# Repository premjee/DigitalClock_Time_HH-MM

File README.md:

# DigitalClock_Time_HH-MM
Displays time in HH:MM format using 7seg led
8 bit microcontroller is used to set and read time from RTC and display time in 7 segment LED.
Schematic of the project is addeded

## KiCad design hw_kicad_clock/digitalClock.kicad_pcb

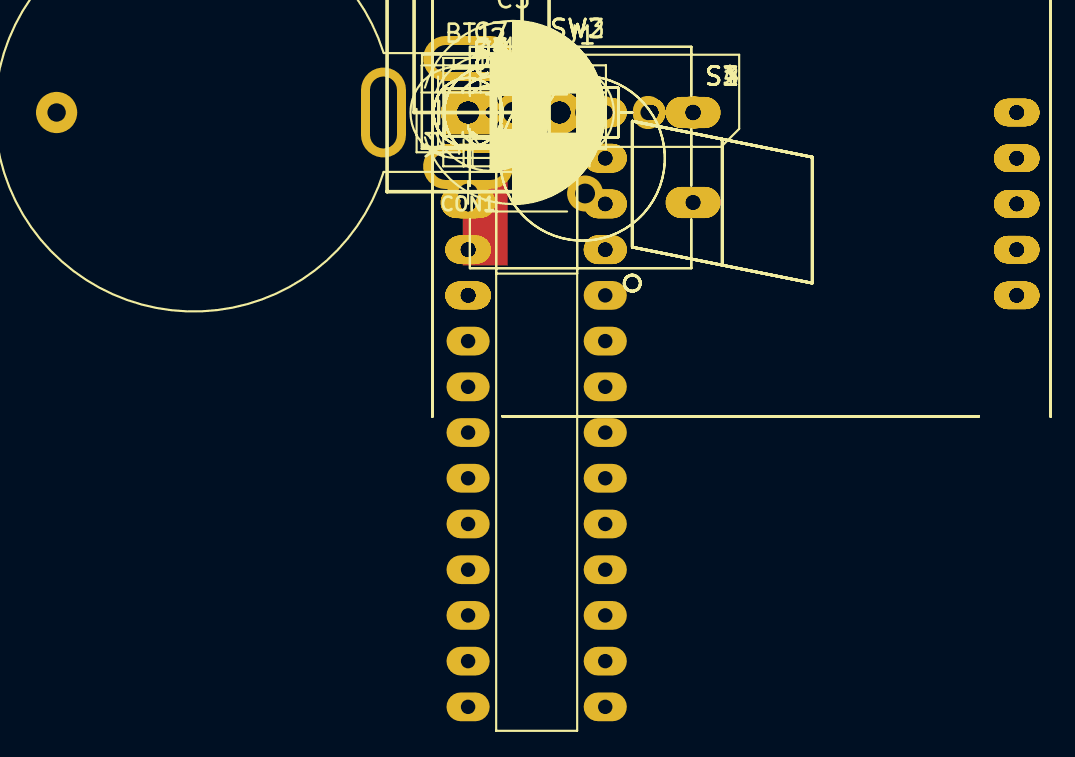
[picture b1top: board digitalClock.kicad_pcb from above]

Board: 2 copper layers, 45 parts (0 on the bottom side), 37 nets, no tracks yet.

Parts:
BT1: BATTERY; BatteryHolder_CR2032H
C1, C2, C6, C8: 100nF; C_Disc_D5.0mm_W2.5mm_P2.50mm
C3, C4: 22pF; C_Disc_D5.0mm_W2.5mm_P2.50mm
C5: 470uF/50v; CP_Radial_D10.0mm_P5.00mm
C7: 220uF/16v; CP_Radial_D6.3mm_P2.50mm
CON1: BARREL_JACK; CUI-PJ-102A_dc-barrel-jack
D1, D2, D7: LED; LED_D3.0mm
D3, D4, D5, D6: 1n4007; D_DO-15_P5.08mm_Vertical_AnodeUp
J1: Conn_01x06; Molex_SPOX_5267-06A_1x06_P2.50mm_Vertical
J2: Conn_01x02; Molex_KK-254_AE-6410-02A_1x02_P2.54mm_Vertical
Q1, Q2, Q3, Q4, Q5: BC547; TO-92_Inline_Narrow_Oval
R1, R3, R4: 10k; R_Axial_DIN0207_L6.3mm_D2.5mm_P10.16mm_Horizontal
R2, R5, R6, R7, R8: 10K; R_Axial_DIN0207_L6.3mm_D2.5mm_P10.16mm_Horizontal
R9: 1k; R_Axial_DIN0207_L6.3mm_D2.5mm_P10.16mm_Horizontal
S1, S2, S3, S4: 7SEGM; 7SegmentLED_1inch
SW1: SW_PUSH; SW_PUSH_6mm
SW2, SW3: SW_PUSH; SW_PUSH-12mm
U1: DS1307+; DIP-8_W7.62mm_LongPads
U2: PIC16F886-I/P; DIP-28_W7.62mm_LongPads
U3: LM7805CT; TO-220-3_Vertical
X1: 32.768 kHz; Crystal_DS26_D2.0mm_L6.0mm_Horizontal_1EP_style1
X2: 20MHz; Crystal_HC18-U_Vertical

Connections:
+5V: C2.1, C7.1, C8.1, J1.2, R1.1, R2.1, R3.2, R5.1, R6.1, R7.1, R8.1, R9.2, U1.8, U2.20, U3.3
/TimeDisplay/SEG_A: S1.7, S2.7, S3.7, S4.7, U2.2
/TimeDisplay/SEG_B: S1.6, S2.6, S3.6, S4.6, U2.3
/TimeDisplay/SEG_C: S1.4, S2.4, S3.4, S4.4, U2.4
/TimeDisplay/SEG_D: S1.2, S2.2, S3.2, S4.2, U2.5
/TimeDisplay/SEG_E: S1.1, S2.1, S3.1, S4.1, U2.6
/TimeDisplay/SEG_F: S1.9, S2.9, S3.9, S4.9, U2.7
/TimeDisplay/SEG_G: S1.10, S2.10, S3.10, S4.10, U2.11
/pic16f886_clock/CC_HRS_H: Q1.2, U2.26
/pic16f886_clock/CC_HRS_L: Q2.2, U2.25
/pic16f886_clock/CC_MIN_H: Q4.2, U2.24
/pic16f886_clock/CC_MIN_L: Q5.2, U2.23
/pic16f886_clock/I2C_SCL: R5.2, U1.6, U2.14
/pic16f886_clock/I2C_SDA: R6.2, U1.5, U2.15
/pic16f886_clock/hrs_sw: R7.2, SW3.1, U2.13
/pic16f886_clock/icsp_clk: J1.5, U2.27
/pic16f886_clock/icsp_dat: J1.4, U2.28
/pic16f886_clock/mclr: J1.1, R4.1, U2.1
/pic16f886_clock/min_sw: R8.2, SW2.1, U2.12
/rtc/SQW_OP: Q3.2, R1.2, U1.7
GND: BT1.2, C1.2, C2.2, C3.1, C4.1, C5.2, C6.2, C7.2, C8.2, D4.2, D5.2, D7.2, J1.3, Q1.3, Q2.3, Q3.3, Q4.3, Q5.3, SW1.1, SW2.2, SW3.2, U1.4, U2.8, U2.19, U3.2
unnamed: BT1.1, U1.3
unnamed: C1.1, R3.1, R4.2, SW1.2
unnamed: C3.2, U2.10, X2.1
unnamed: C4.2, U2.9, X2.2
unnamed: C5.1, C6.1, D3.1, D6.1, U3.1
unnamed: CON1.1, D3.2, D4.1, J2.2
unnamed: CON1.2, D5.1, D6.2, J2.1
unnamed: D1.1, D2.1, R2.2
unnamed: D1.2, D2.2, Q3.1
unnamed: D7.1, R9.1
unnamed: Q1.1, S1.3, S1.8
unnamed: Q2.1, S2.3, S2.8
unnamed: Q4.1, S3.3, S3.8
unnamed: Q5.1, S4.3, S4.8
unnamed: U1.1, X1.2
unnamed: U1.2, X1.1

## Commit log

2017-12-18 Source code for digital timer using RTC ds1307 & uc pic16f886. Communication to RTC is by IIC bitband implementation.
2017-12-18 modified to test 7 seg leds
2017-12-18 Production release code is enabled in order to set RTC parameters
2017-12-18 schematic for digital clock is added
2017-12-19 appended with recent changes
2018-01-12 Communication to DS1307 is established using I2C peripheral registers. Both interrupt and polling method is implemented. Production release code for setting RTC for the first time is removed. Now RTC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
2018-01-12 information in readme is modified
2018-01-16 changes includes for enabling watchdog timer
